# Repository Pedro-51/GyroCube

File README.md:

# GyroCube
 Self Balancing Cube Project

Balancing Cube project based on the "remrc" model: https://www.thingiverse.com/thing:6695891

    Creation of an Application to facilitate calibration and motor testing,
    Merging the main program with the motors test program,
	Creation of a printed circuit for those who wish to have a beautiful object,
    Addition of a Power button,
    Addition of a button to turn on the LEDs and change their colors,
    Modified the face files for placing the switches in 12 and 16mm. Thanks to dinomight.

	Maj 26/11/08: The cube can now stand on all three sides (Can be disabled in ESP32.h),
				  Improved stability,
				  French and English languages in the same App and program (edit to do in ESP32.h),

Explanatory video: https://youtu.be/zuOgj580Nhk<br>
Led function video: https://youtu.be/vczHyelNjr4<br>
PCB: https://www.pcbway.com/project/shareproject/GyroCube_v1_1_5d583cf0.html<br>
Android app: [(Appli%20APK/Cube_1_02.apk)<br>

#######################################################################################

For the program to work, you need to install esp32 by expressif v2.0.17 board version

#######################################################################################

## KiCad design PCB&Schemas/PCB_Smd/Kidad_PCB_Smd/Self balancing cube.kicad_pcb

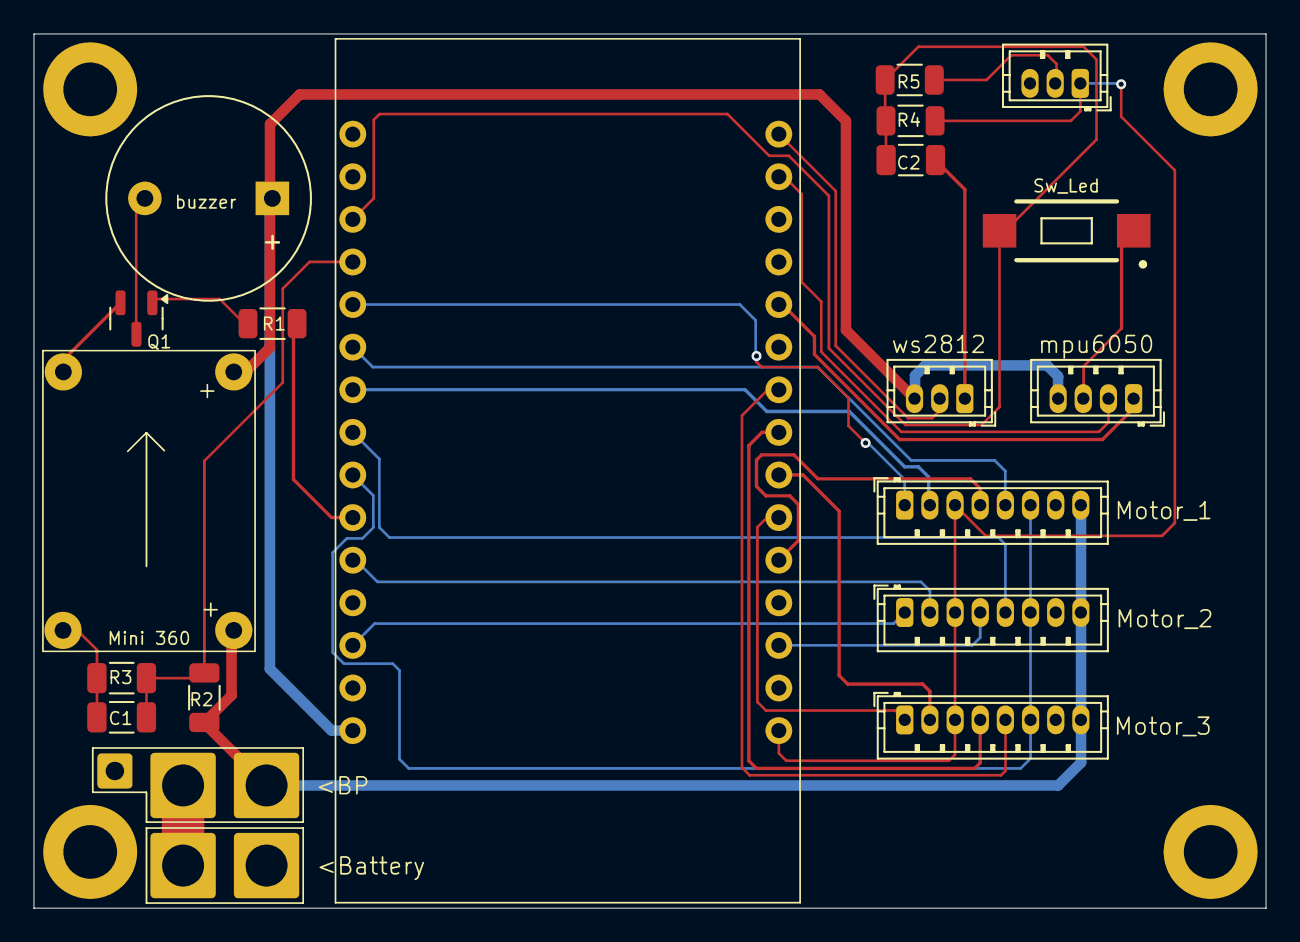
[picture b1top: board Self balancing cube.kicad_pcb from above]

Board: 2 copper layers, 73.5 x 52.1 mm, 27 parts (0 on the bottom side), 27 nets.

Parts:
BZ1: Buzzer; Buzzer_12x9.5RM7.6
C1, C2: 100nf; C_1206_3216Metric
H1, H2, H3, H4: MountingHole; MountingHole_3.2mm_M3_DIN965_Pad
J1, J2, J3, J4: Conn_01x01; SolderWire-2sqmm_1x01_D2mm_OD3.9mm
J5: Conn_01x01; SolderWire-0.5sqmm_1x01_D0.9mm_OD2.1mm
J6, J7, J8: Conn_01x08_Pin; JST_ZH_B8B-ZR_1x08_P1.50mm_Vertical
J12: Conn_01x04_Pin; JST_ZH_B4B-ZR_1x04_P1.50mm_Vertical
J13, J14: Conn_01x03_Pin; JST_ZH_B3B-ZR_1x03_P1.50mm_Vertical
Q1: MMBT2222A; SOT-23
R1, R5: 1k; R_1206_3216Metric
R2: 33k; C_1206_3216Metric
R3: 10k; C_1206_3216Metric
R4: 10k; R_1206_3216Metric
SW2: SW_Push; SW_RS-032G05A3-SMRT
U1: 5v; DCDC buck
U2: esp module 30pins

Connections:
+3.3V: J6.3, J7.3, J8.3, J14.1, R4.2, U2.16 (3V3)
+5V: BZ1.1 (+), J12.4, J13.3, U1.3 (OUT+), U2.15 (VIN)
+BATT: J1.1, J6.8, J7.8, J8.8, R2.1, U1.1 (IN+)
-BATT: C1.2, C2.2, H1.1, H2.1, H3.1, H4.1, J4.1, J5.1, J6.7, J7.7, J8.7, J12.3, J13.1, J14.3, Q1.2 (E), R3.2, SW2.1, U1.2 (IN-), U1.4 (OUT-), U2.14 (GND)
Adc batt: C1.1, R2.2, R3.1, U2.4 (D34)
unnamed: BZ1.2 (-), Q1.3 (C)
unnamed: J2.1, J3.1
unnamed: J6.1, U2.5 (D35)
unnamed: J6.2, U2.7 (D33)
unnamed: J6.4, U2.20 (D4)
unnamed: J6.5, U2.6 (D32)
unnamed: J6.6, J7.6, J8.6, U2.9 (D26)
unnamed: J7.1, U2.13 (D13)
unnamed: J7.2, U2.11 (D14)
unnamed: J7.4, U2.18 (D15)
unnamed: J7.5, U2.8 (D25)
unnamed: J8.1, U2.21 (RX2)
unnamed: J8.2, U2.22 (TX2)
unnamed: J8.4, U2.23 (D5)
unnamed: J8.5, U2.24 (D18)
unnamed: J14.2, R5.1
unnamed: Q1.1 (B), R1.2
Push_Led: C2.1, R4.1, R5.2, SW2.2, U2.3 (VN)
SCL: J12.2, U2.29 (D22)
SDA: J12.1, U2.26 (D21)
WS2812: J13.2, U2.30 (D23)
cmd buzzer: R1.1, U2.10 (D27)

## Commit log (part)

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2024-11-12 Version 1.10
2024-11-12 First README
2024-12-05 new BLE firmware with browser based config tool
2024-12-05 updating readme
2024-12-05 updating readme -fixing qr code size
2024-12-05 fixing image size
2024-12-05 adding link to pcbway
2024-12-05 more readme linking
2024-12-06 v1.0 firmware. adding version checking, and motor remapping
2024-12-06 don't track .DS_Store files
2024-12-06 changine html file name to match cdn
2024-12-06 balancing icon adjustment
2024-12-07 adding led colors to web interface, fixing motor testing progress
2024-12-08 fixing alert loop
2025-02-14 Version 1.11
    Added schematic to facilitate assembly, modified program to check if motors are properly connected to the board.
2025-02-14 Update BOM
2025-02-14 Version 1.11
    Update
2025-02-14 Version 1.11
2025-06-16 Fix BLE web tool hosting
2025-06-16 Rename to index.html
2025-06-16 Rename pages --> docs
2025-06-16 Fix casing on web tool URL
2025-07-20 Version 1.13
    Modified the printed circuit board and created a PCB for through-hole components.
    Bug fixes in the program.
2025-07-24 Version 1.13.1
2025-07-28 Version 1.12
2025-08-04 Correction PCB

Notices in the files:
PCB&Schemas/PCB_Smd/Kidad_PCB_Smd/Self balancing cube.kicad_pcb:
Licence CC BY-NC
